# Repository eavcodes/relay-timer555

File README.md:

# relay-timer555
Adjustable timer circuit with 555 and relay switch

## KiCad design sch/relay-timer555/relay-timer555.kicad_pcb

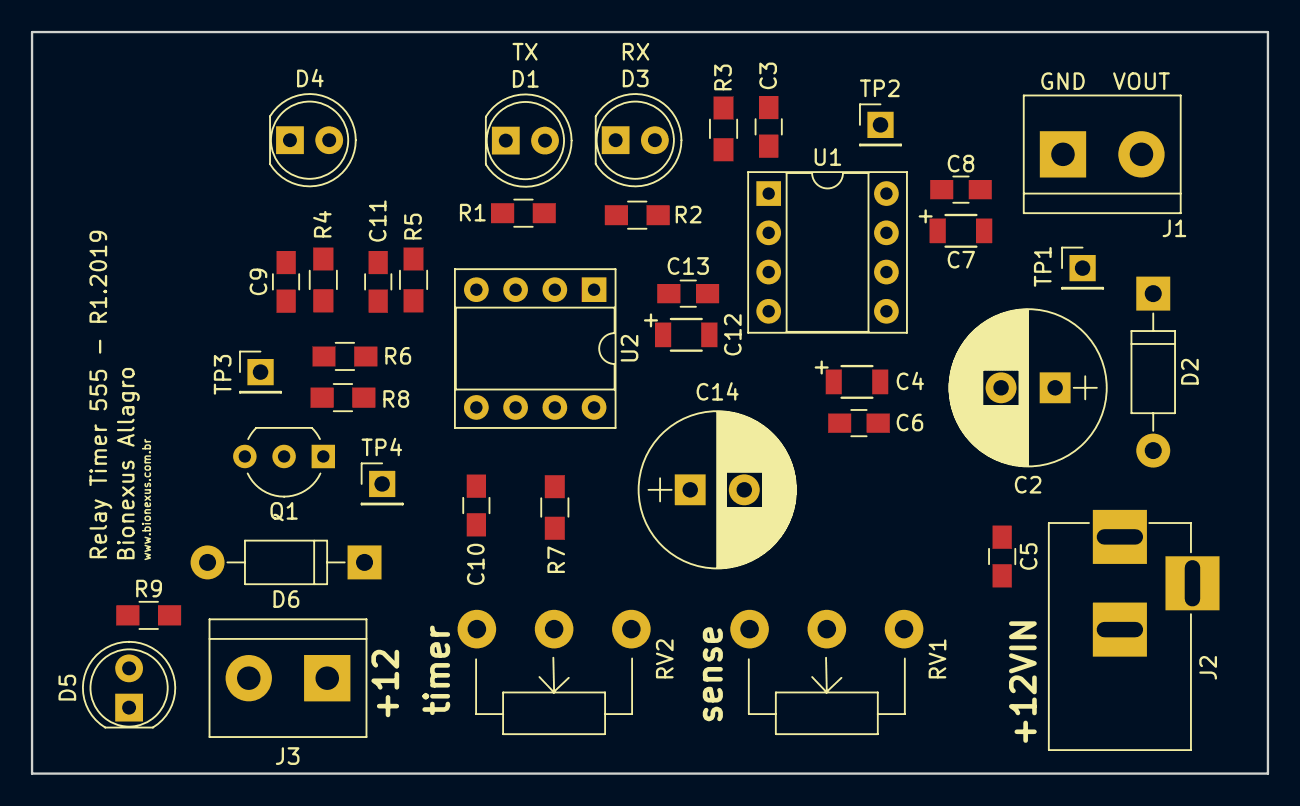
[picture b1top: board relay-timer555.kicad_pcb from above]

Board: 2 copper layers, 80.0 x 48.0 mm, 40 parts (0 on the bottom side), 17 nets, no tracks yet.

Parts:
C2, C14: 470uF; CP_Radial_D10.0mm_P3.50mm
C3, C5, C6, C8, C9, C11, C13: 0.1uF; C_0805_HandSoldering
C4, C7, C12: c_pol_1206
C10: 10nF; C_0805_HandSoldering
D1: IR204A; LED_D5.0mm
D2: 1N4007; D_DO-41_SOD81_P10.16mm_Horizontal
D3: D_Photo; LED_D5.0mm
D4: TRIG; LED_D5.0mm
D5: ON; LED_D5.0mm
D6: 1N4004; D_DO-41_SOD81_P10.16mm_Horizontal
J1: PWROUT; TerminalBlock_bornier-2_P5.08mm
J2: PWRIN; BARREL_JACK
J3: RPORT; TerminalBlock_bornier-2_P5.08mm
Q1: 2N3904; TO-92_Inline_Wide
R1: 220R; R_0805_HandSoldering
R2, R6: 10k; R_0805_HandSoldering
R3: 470R; R_0805_HandSoldering
R4, R9: 1k5; R_0805_HandSoldering
R5, R8: 1k; R_0805_HandSoldering
R7: 120k; R_0805_HandSoldering
RV1: 100k; Potentiometer_WirePads_largePads
RV2: 1M; Potentiometer_WirePads_largePads
TP1, TP2, TP3, TP4: TestPoint; Pin_Header_Straight_1x01_Pitch2.54mm
U1: LM741; DIP-8_W7.62mm_Socket
U2: LM555; DIP-8_W7.62mm_Socket

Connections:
+12V: C2.1, C5.1, C7.1, C8.1, C12.1, C13.1, D2.1, D6.1, J1.2, J3.1, R1.2, R2.2, R5.2, R9.2, RV1.1, RV2.1, TP1.1, U1.7, U2.8
GND: C2.2, C3.2, C4.2, C5.2, C6.2, C7.2, C8.2, C9.2, C10.2, C11.2, C12.2, C13.2, C14.2, D1.1, D3.2, D4.1, J1.1, J2.2, J2.3, Q1.1, R6.1, RV1.3, U1.4, U2.1
unnamed: C3.1, R3.1, TP2.1, U1.2
unnamed: C4.1, C6.1, RV1.2, U1.3
unnamed: C9.1, R4.2, TP3.1, U1.6, U2.2
unnamed: C10.1, U2.5
unnamed: C11.1, R5.1, U2.4
unnamed: C14.1, R7.2, U2.6, U2.7
unnamed: D1.2, R1.1
unnamed: D2.2, J2.1
unnamed: D3.1, R2.1, R3.2
unnamed: D4.2, R4.1
unnamed: D5.1, D6.2, J3.2, Q1.3
unnamed: D5.2, R9.1
unnamed: Q1.2, R8.1
unnamed: R6.2, R8.2, TP4.1, U2.3
unnamed: R7.1, RV2.2, RV2.3

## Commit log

2019-06-30 rev1 sch and pcb
